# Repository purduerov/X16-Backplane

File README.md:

# Readme for X16-Backplane
This board routes signals and power between all the boards

Whenever you make a new part, download the datasheet and save it here _**and**_ with the part in the parts library

Always pull other people's changes before beginning to work
`git pull`

Be sure to push your changes after  working on them. Run:
1. `git add .` to add any files in this directory or a subdirectory
or `git add -u` to add any modified files
2. (Optional) `git clean -nX` to see what ignored files can be removed
	`git clean -fX` removes ignored files (Eagle backups)
3. `git commit -m "helpful commit message"` with a description of the work that you did
4. `git push` to push your work to github

Other helpful commands
* `git status` says information about modified and staged files
* `git log` shows the recent commits of the repository
* `git log filename.extension` show the recent commits for just that file
* `git checkout first-couple-letter-of-commit-id` lets you go back to a previous version
* `git checkout master` brings you back to the latest commit
* `git tag` lists the tags
* `git tag -a orderX -m "the version of the board placed for the X'th order"` tag a specific commit
* `git push --tags` needed to push tags to remote
* `git show orderX` show the commit log for the given tag
* `git checkout orderX` go back and interact with the files at the tagged commit

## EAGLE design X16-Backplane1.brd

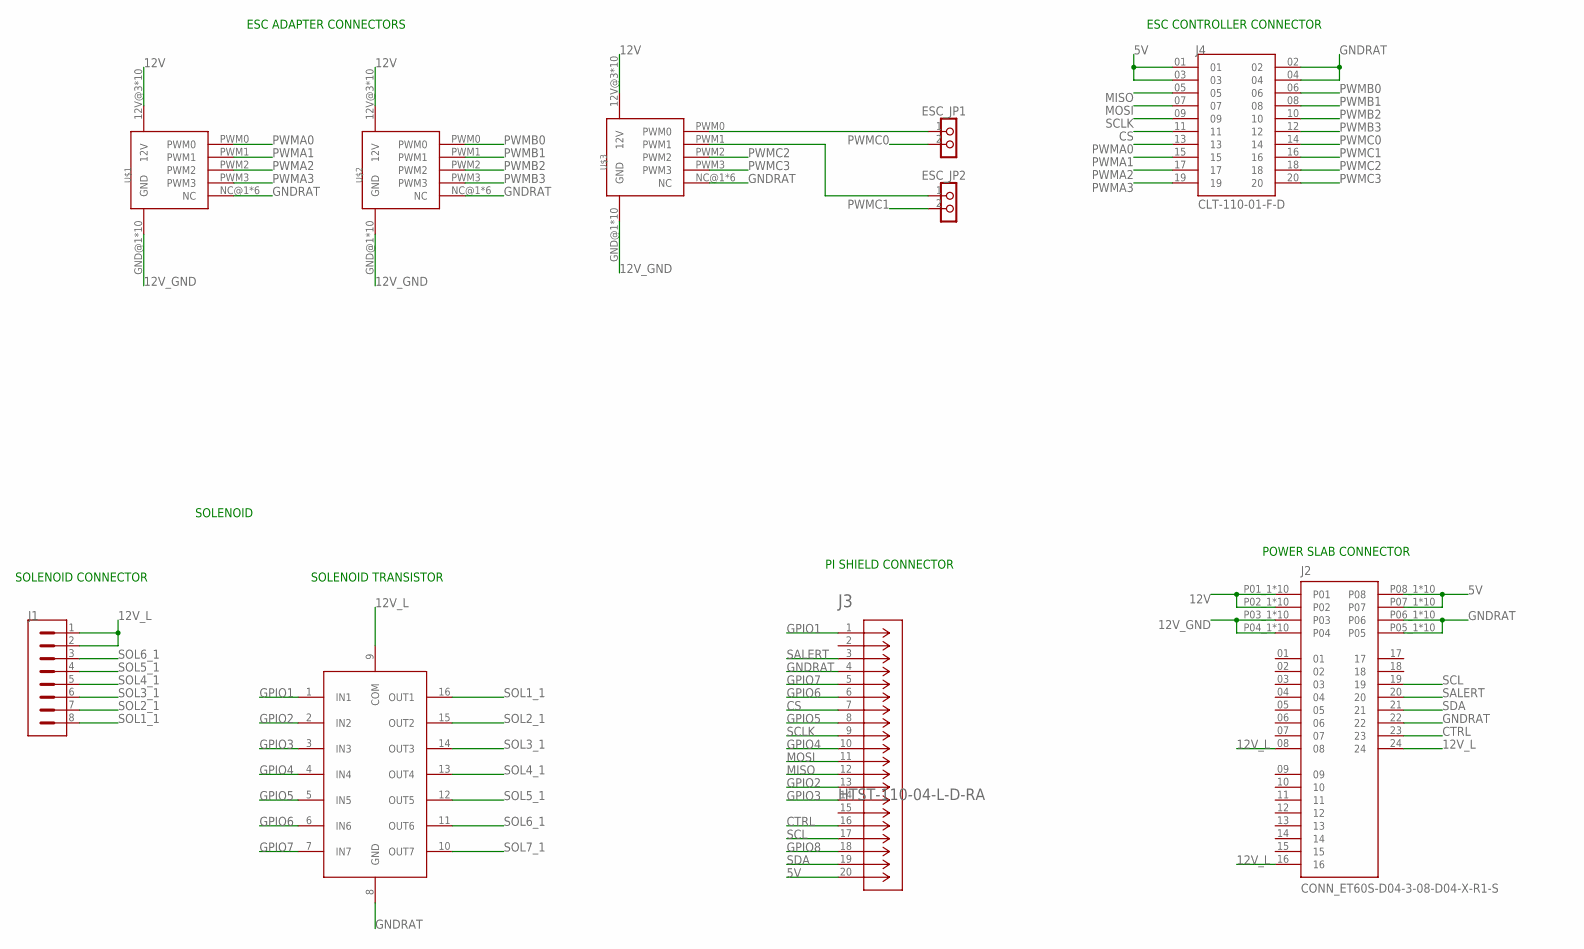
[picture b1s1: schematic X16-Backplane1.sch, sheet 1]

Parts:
ESC_JP1, ESC_JP2: TEST_PIN-1X2; 1X02
J1: CONN_PXC-8-RA-1778683; PXC-8-RA-1778683
J2: CONN_ET60S-D04-3-08-D04-X-R1-S; SAMTEC_ET60S-D04-3-08-D04-X-R1-S
J3: HTST-110-04-L-D-RA; CONN_HTST-110-04/05-X-D-RA_SAI
J4: CLT-110-01-F-D; SAMTEC_CLT-110-01-F-D
U2: TRANS_ULN2003AD; 16-SOIC
U$1, U$2, U$3: CONN_BACKPLANE_ESC_ADAPTER_NEW; CONN_BACKPLANE_ESC_ADAPTER

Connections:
5V: J2.P07_1 (P07), J2.P07_2 (P07), J2.P07_3 (P07), J2.P07_4 (P07), J2.P07_5 (P07), J2.P07_6 (P07), J2.P07_7 (P07), J2.P07_8 (P07), J2.P07_9 (P07), J2.P07_10 (P07), J2.P08_1 (P08), J2.P08_2 (P08), J2.P08_3 (P08), J2.P08_4 (P08), J2.P08_5 (P08), J2.P08_6 (P08), J2.P08_7 (P08), J2.P08_8 (P08), J2.P08_9 (P08), J2.P08_10 (P08), J3.20, J4.01, J4.03; also elsewhere on the board
12V: J2.P01_1 (P01), J2.P01_2 (P01), J2.P01_3 (P01), J2.P01_4 (P01), J2.P01_5 (P01), J2.P01_6 (P01), J2.P01_7 (P01), J2.P01_8 (P01), J2.P01_9 (P01), J2.P01_10 (P01), J2.P02_1 (P02), J2.P02_2 (P02), J2.P02_3 (P02), J2.P02_4 (P02), J2.P02_5 (P02), J2.P02_6 (P02), J2.P02_7 (P02), J2.P02_8 (P02), J2.P02_9 (P02), J2.P02_10 (P02), U$1.12V@3 (12V), U$1.12V@4 (12V), U$1.12V@5 (12V), U$1.12V@6 (12V), U$1.12V@7 (12V), U$1.12V@8 (12V), U$1.12V@9 (12V), U$1.12V@10 (12V), U$1.12V@11 (12V), U$1.12V@12 (12V), U$2.12V@3 (12V), U$2.12V@4 (12V), U$2.12V@5 (12V), U$2.12V@6 (12V), U$2.12V@7 (12V), U$2.12V@8 (12V), U$2.12V@9 (12V), U$2.12V@10 (12V), U$2.12V@11 (12V), U$2.12V@12 (12V), U$3.12V@3 (12V), U$3.12V@4 (12V), U$3.12V@5 (12V), U$3.12V@6 (12V), U$3.12V@7 (12V), U$3.12V@8 (12V), U$3.12V@9 (12V), U$3.12V@10 (12V), U$3.12V@11 (12V), U$3.12V@12 (12V); also elsewhere on the board
12V_GND: J2.P03_1 (P03), J2.P03_2 (P03), J2.P03_3 (P03), J2.P03_4 (P03), J2.P03_5 (P03), J2.P03_6 (P03), J2.P03_7 (P03), J2.P03_8 (P03), J2.P03_9 (P03), J2.P03_10 (P03), J2.P04_1 (P04), J2.P04_2 (P04), J2.P04_3 (P04), J2.P04_4 (P04), J2.P04_5 (P04), J2.P04_6 (P04), J2.P04_7 (P04), J2.P04_8 (P04), J2.P04_9 (P04), J2.P04_10 (P04), U$1.GND@1 (GND), U$1.GND@2 (GND), U$1.GND@3 (GND), U$1.GND@4 (GND), U$1.GND@5 (GND), U$1.GND@6 (GND), U$1.GND@7 (GND), U$1.GND@8 (GND), U$1.GND@9 (GND), U$1.GND@10 (GND), U$2.GND@1 (GND), U$2.GND@2 (GND), U$2.GND@3 (GND), U$2.GND@4 (GND), U$2.GND@5 (GND), U$2.GND@6 (GND), U$2.GND@7 (GND), U$2.GND@8 (GND), U$2.GND@9 (GND), U$2.GND@10 (GND), U$3.GND@1 (GND), U$3.GND@2 (GND), U$3.GND@3 (GND), U$3.GND@4 (GND), U$3.GND@5 (GND), U$3.GND@6 (GND), U$3.GND@7 (GND), U$3.GND@8 (GND), U$3.GND@9 (GND), U$3.GND@10 (GND); also elsewhere on the board
12V_L: J1.1, J1.2, J2.08, J2.16, J2.24, U2.9 (COM)
CS: J3.7, J4.11; also elsewhere on the board
CTRL: J2.23, J3.16
GNDRAT: J2.22, J2.P05_1 (P05), J2.P05_2 (P05), J2.P05_3 (P05), J2.P05_4 (P05), J2.P05_5 (P05), J2.P05_6 (P05), J2.P05_7 (P05), J2.P05_8 (P05), J2.P05_9 (P05), J2.P05_10 (P05), J2.P06_1 (P06), J2.P06_2 (P06), J2.P06_3 (P06), J2.P06_4 (P06), J2.P06_5 (P06), J2.P06_6 (P06), J2.P06_7 (P06), J2.P06_8 (P06), J2.P06_9 (P06), J2.P06_10 (P06), J3.4, J4.02, J4.04, U2.8 (GND), U$1.NC@1 (NC), U$1.NC@2 (NC), U$1.NC@3 (NC), U$1.NC@4 (NC), U$1.NC@5 (NC), U$1.NC@6 (NC), U$2.NC@1 (NC), U$2.NC@2 (NC), U$2.NC@3 (NC), U$2.NC@4 (NC), U$2.NC@5 (NC), U$2.NC@6 (NC), U$3.NC@1 (NC), U$3.NC@2 (NC), U$3.NC@3 (NC), U$3.NC@4 (NC), U$3.NC@5 (NC), U$3.NC@6 (NC); also elsewhere on the board
GPIO1: J3.1, U2.1 (IN1)
GPIO2: J3.13, U2.2 (IN2)
GPIO3: J3.14, U2.3 (IN3)
GPIO4: J3.10, U2.4 (IN4)
GPIO5: J3.8, U2.5 (IN5)
GPIO6: J3.6, U2.6 (IN6)
GPIO7: J3.5, U2.7 (IN7)
GPIO8: J3.18
MISO: J3.12, J4.05; also elsewhere on the board
MOSI: J3.11, J4.07; also elsewhere on the board
unnamed: ESC_JP1.1, U$3.PWM0
unnamed: ESC_JP2.1, U$3.PWM1
PWMA0: J4.13, U$1.PWM0
PWMA1: J4.15, U$1.PWM1
PWMA2: J4.17, U$1.PWM2
PWMA3: J4.19, U$1.PWM3
PWMB0: J4.06, U$2.PWM0
PWMB1: J4.08, U$2.PWM1
PWMB2: J4.10, U$2.PWM2
PWMB3: J4.12, U$2.PWM3
PWMC0: ESC_JP1.2, J4.14; also elsewhere on the board
PWMC1: ESC_JP2.2, J4.16; also elsewhere on the board
PWMC2: J4.18, U$3.PWM2
PWMC3: J4.20, U$3.PWM3
SALERT: J2.20, J3.3
SCL: J2.19, J3.17
SCLK: J3.9, J4.09; also elsewhere on the board
SDA: J2.21, J3.19
SOL1_1: J1.8, U2.16 (OUT1)
SOL2_1: J1.7, U2.15 (OUT2)
SOL3_1: J1.6, U2.14 (OUT3)
SOL4_1: J1.5, U2.13 (OUT4)
SOL5_1: J1.4, U2.12 (OUT5)
SOL6_1: J1.3, U2.11 (OUT6)
SOL7_1: U2.10 (OUT7)

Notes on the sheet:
ESC ADAPTER CONNECTORS
SOLENOID
POWER SLAB CONNECTOR
SOLENOID TRANSISTOR
SOLENOID CONNECTOR
ESC CONTROLLER CONNECTOR
PI SHIELD CONNECTOR

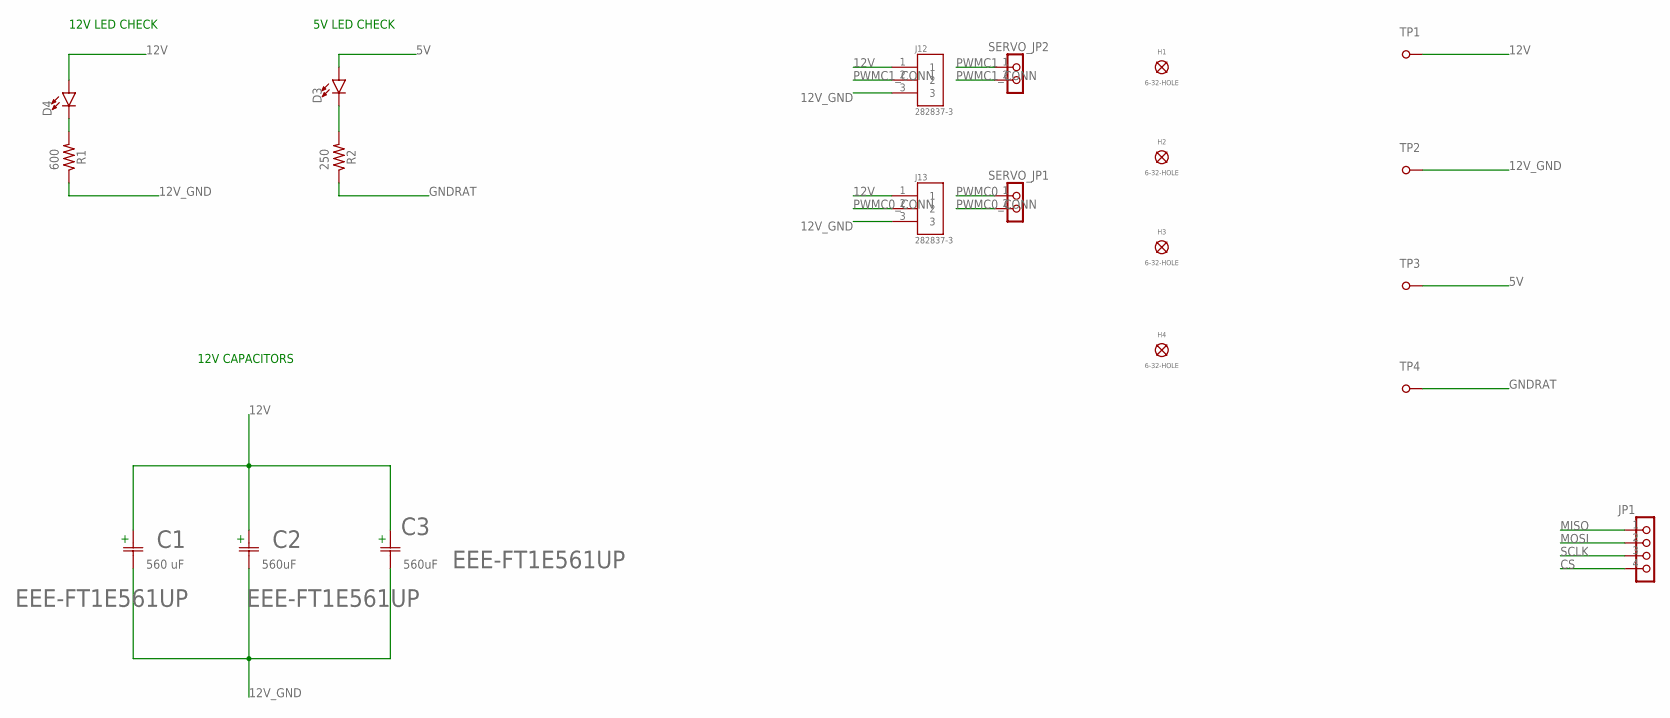
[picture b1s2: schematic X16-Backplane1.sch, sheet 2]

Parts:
C1, C2, C3: EEE-FT1E561UP; CAP_FT_F_PAN
D3, D4: LEDCHIPLED_0805; CHIPLED_0805
H1, H2, H3, H4: 6-32-HOLE
J12, J13: 282837-3; TE_282837-3
JP1: TEST_PIN-1X4; 1X04
R1, R2: 0603
SERVO_JP1, SERVO_JP2: TEST_PIN-1X2; 1X02
TP1, TP2, TP3, TP4: TESTPOINT_5.04MM

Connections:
5V: D3.A, TP3.TP; also elsewhere on the board
12V: C1.1, C2.1, C3.1, D4.A, J12.1, J13.1, TP1.TP; also elsewhere on the board
12V_GND: C1.2, C2.2, C3.2, J12.3, J13.3, R1.1, TP2.TP; also elsewhere on the board
CS: JP1.4; also elsewhere on the board
GNDRAT: R2.1, TP4.TP; also elsewhere on the board
MISO: JP1.1; also elsewhere on the board
MOSI: JP1.2; also elsewhere on the board
unnamed: D4.C, R1.2
unnamed: D3.C, R2.2
PWMC0: SERVO_JP1.1; also elsewhere on the board
PWMC0_CONN: J13.2, SERVO_JP1.2
PWMC1: SERVO_JP2.1; also elsewhere on the board
PWMC1_CONN: J12.2, SERVO_JP2.2
SCLK: JP1.3; also elsewhere on the board

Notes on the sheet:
12V LED CHECK
5V LED CHECK
12V CAPACITORS

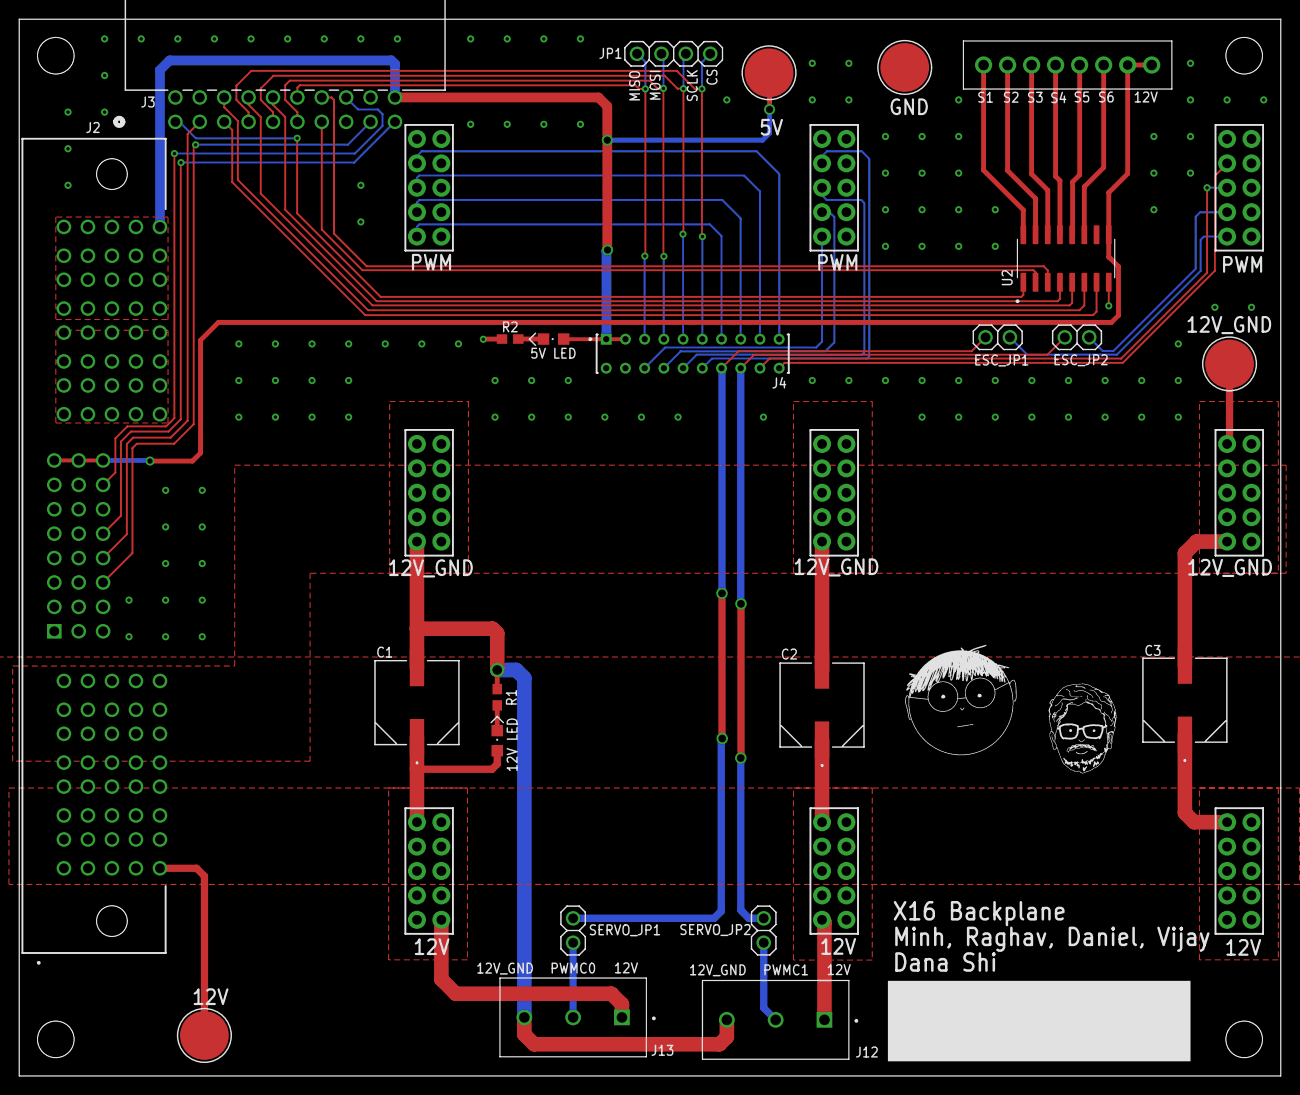
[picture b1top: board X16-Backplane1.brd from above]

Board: 2 copper layers, 131.3 x 110.0 mm, 30 parts (0 on the bottom side), 44 nets.

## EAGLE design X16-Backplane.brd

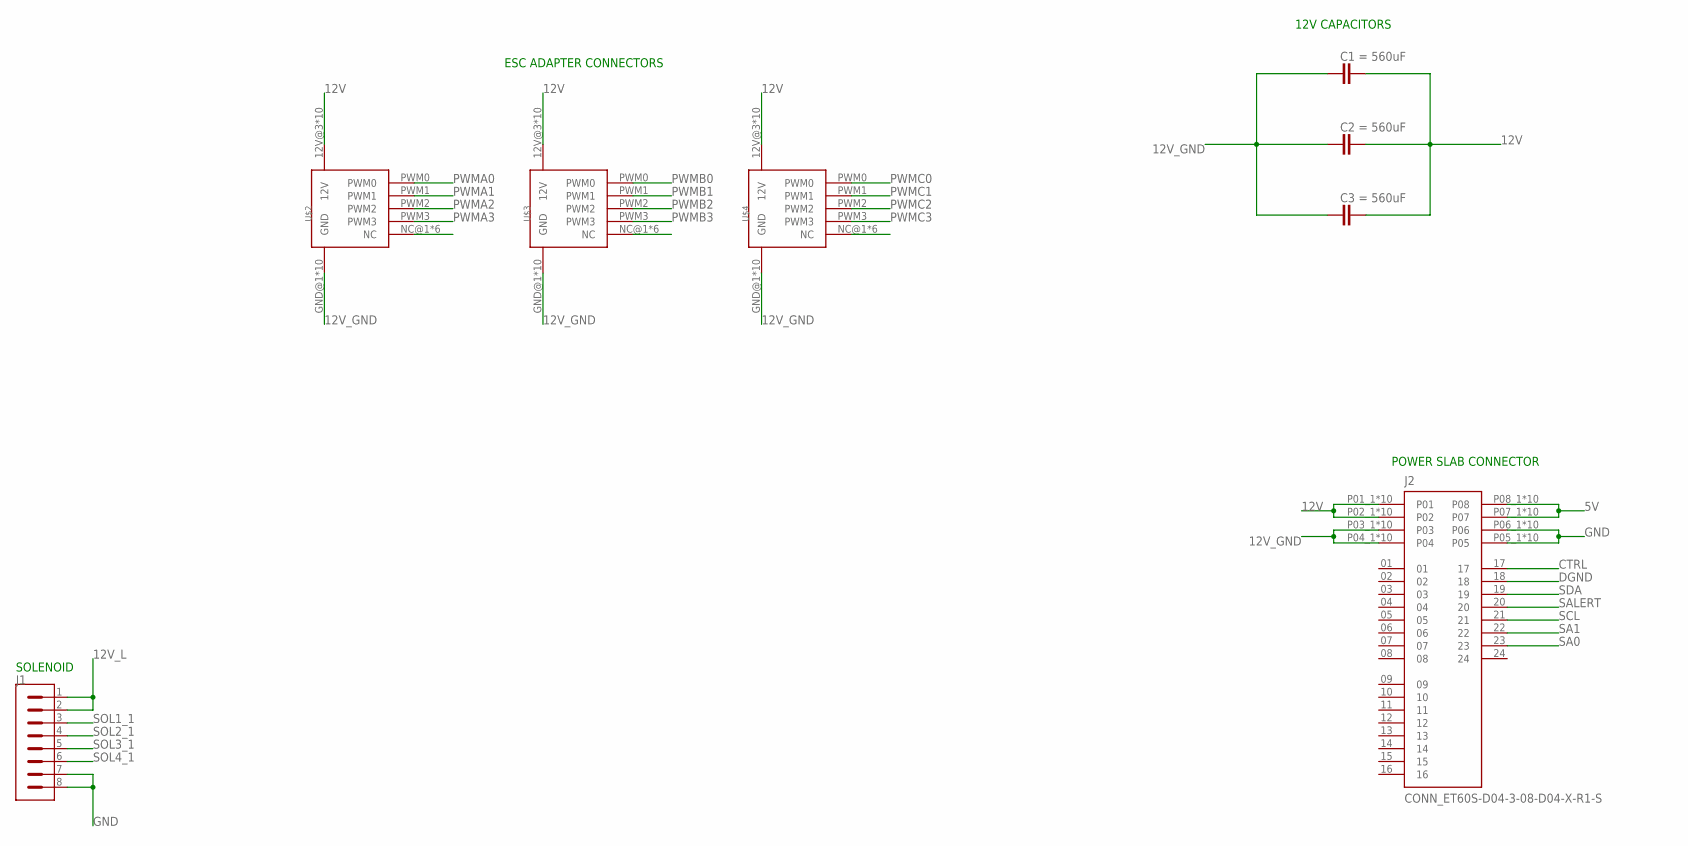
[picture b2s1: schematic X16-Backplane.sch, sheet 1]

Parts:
J1: CONN_PXC-8-RA-1778683; PXC-8-RA-1778683
J2: CONN_ET60S-D04-3-08-D04-X-R1-S; SAMTEC_ET60S-D04-3-08-D04-X-R1-S
U$2, U$3, U$4: CONN_BACKPLANE_ESC_ADAPTER

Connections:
5V: J2.P07_1 (P07), J2.P07_2 (P07), J2.P07_3 (P07), J2.P07_4 (P07), J2.P07_5 (P07), J2.P07_6 (P07), J2.P07_7 (P07), J2.P07_8 (P07), J2.P07_9 (P07), J2.P07_10 (P07), J2.P08_1 (P08), J2.P08_2 (P08), J2.P08_3 (P08), J2.P08_4 (P08), J2.P08_5 (P08), J2.P08_6 (P08), J2.P08_7 (P08), J2.P08_8 (P08), J2.P08_9 (P08), J2.P08_10 (P08); also elsewhere on the board
12V: J2.P01_1 (P01), J2.P01_2 (P01), J2.P01_3 (P01), J2.P01_4 (P01), J2.P01_5 (P01), J2.P01_6 (P01), J2.P01_7 (P01), J2.P01_8 (P01), J2.P01_9 (P01), J2.P01_10 (P01), J2.P02_1 (P02), J2.P02_2 (P02), J2.P02_3 (P02), J2.P02_4 (P02), J2.P02_5 (P02), J2.P02_6 (P02), J2.P02_7 (P02), J2.P02_8 (P02), J2.P02_9 (P02), J2.P02_10 (P02), U$2.12V@3 (12V), U$2.12V@4 (12V), U$2.12V@5 (12V), U$2.12V@6 (12V), U$2.12V@7 (12V), U$2.12V@8 (12V), U$2.12V@9 (12V), U$2.12V@10 (12V), U$2.12V@11 (12V), U$2.12V@12 (12V), U$3.12V@3 (12V), U$3.12V@4 (12V), U$3.12V@5 (12V), U$3.12V@6 (12V), U$3.12V@7 (12V), U$3.12V@8 (12V), U$3.12V@9 (12V), U$3.12V@10 (12V), U$3.12V@11 (12V), U$3.12V@12 (12V), U$4.12V@3 (12V), U$4.12V@4 (12V), U$4.12V@5 (12V), U$4.12V@6 (12V), U$4.12V@7 (12V), U$4.12V@8 (12V), U$4.12V@9 (12V), U$4.12V@10 (12V), U$4.12V@11 (12V), U$4.12V@12 (12V); also elsewhere on the board
12V_GND: J2.P03_1 (P03), J2.P03_2 (P03), J2.P03_3 (P03), J2.P03_4 (P03), J2.P03_5 (P03), J2.P03_6 (P03), J2.P03_7 (P03), J2.P03_8 (P03), J2.P03_9 (P03), J2.P03_10 (P03), J2.P04_1 (P04), J2.P04_2 (P04), J2.P04_3 (P04), J2.P04_4 (P04), J2.P04_5 (P04), J2.P04_6 (P04), J2.P04_7 (P04), J2.P04_8 (P04), J2.P04_9 (P04), J2.P04_10 (P04), U$2.GND@1 (GND), U$2.GND@2 (GND), U$2.GND@3 (GND), U$2.GND@4 (GND), U$2.GND@5 (GND), U$2.GND@6 (GND), U$2.GND@7 (GND), U$2.GND@8 (GND), U$2.GND@9 (GND), U$2.GND@10 (GND), U$3.GND@1 (GND), U$3.GND@2 (GND), U$3.GND@3 (GND), U$3.GND@4 (GND), U$3.GND@5 (GND), U$3.GND@6 (GND), U$3.GND@7 (GND), U$3.GND@8 (GND), U$3.GND@9 (GND), U$3.GND@10 (GND), U$4.GND@1 (GND), U$4.GND@2 (GND), U$4.GND@3 (GND), U$4.GND@4 (GND), U$4.GND@5 (GND), U$4.GND@6 (GND), U$4.GND@7 (GND), U$4.GND@8 (GND), U$4.GND@9 (GND), U$4.GND@10 (GND)
12V_L: J1.1, J1.2; also elsewhere on the board
CTRL: J2.17; also elsewhere on the board
DGND: J2.18; also elsewhere on the board
GND: J1.7, J1.8, J2.P05_1 (P05), J2.P05_2 (P05), J2.P05_3 (P05), J2.P05_4 (P05), J2.P05_5 (P05), J2.P05_6 (P05), J2.P05_7 (P05), J2.P05_8 (P05), J2.P05_9 (P05), J2.P05_10 (P05), J2.P06_1 (P06), J2.P06_2 (P06), J2.P06_3 (P06), J2.P06_4 (P06), J2.P06_5 (P06), J2.P06_6 (P06), J2.P06_7 (P06), J2.P06_8 (P06), J2.P06_9 (P06), J2.P06_10 (P06); also elsewhere on the board
unnamed: U$2.NC@1 (NC), U$2.NC@2 (NC), U$2.NC@3 (NC), U$2.NC@4 (NC), U$2.NC@5 (NC), U$2.NC@6 (NC)
unnamed: U$3.NC@1 (NC), U$3.NC@2 (NC), U$3.NC@3 (NC), U$3.NC@4 (NC), U$3.NC@5 (NC), U$3.NC@6 (NC)
unnamed: U$4.NC@1 (NC), U$4.NC@2 (NC), U$4.NC@3 (NC), U$4.NC@4 (NC), U$4.NC@5 (NC), U$4.NC@6 (NC)
PWMA0: U$2.PWM0
PWMA1: U$2.PWM1
PWMA2: U$2.PWM2
PWMA3: U$2.PWM3
PWMB0: U$3.PWM0
PWMB1: U$3.PWM1
PWMB2: U$3.PWM2
PWMB3: U$3.PWM3
PWMC0: U$4.PWM0
PWMC1: U$4.PWM1
PWMC2: U$4.PWM2
PWMC3: U$4.PWM3
SA0: J2.23; also elsewhere on the board
SA1: J2.22; also elsewhere on the board
SALERT: J2.20; also elsewhere on the board
SCL: J2.21; also elsewhere on the board
SDA: J2.19; also elsewhere on the board
SOL1_1: J1.3; also elsewhere on the board
SOL2_1: J1.4; also elsewhere on the board
SOL3_1: J1.5; also elsewhere on the board
SOL4_1: J1.6; also elsewhere on the board

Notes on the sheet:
SOLENOID
POWER SLAB CONNECTOR
ESC ADAPTER CONNECTORS
12V CAPACITORS

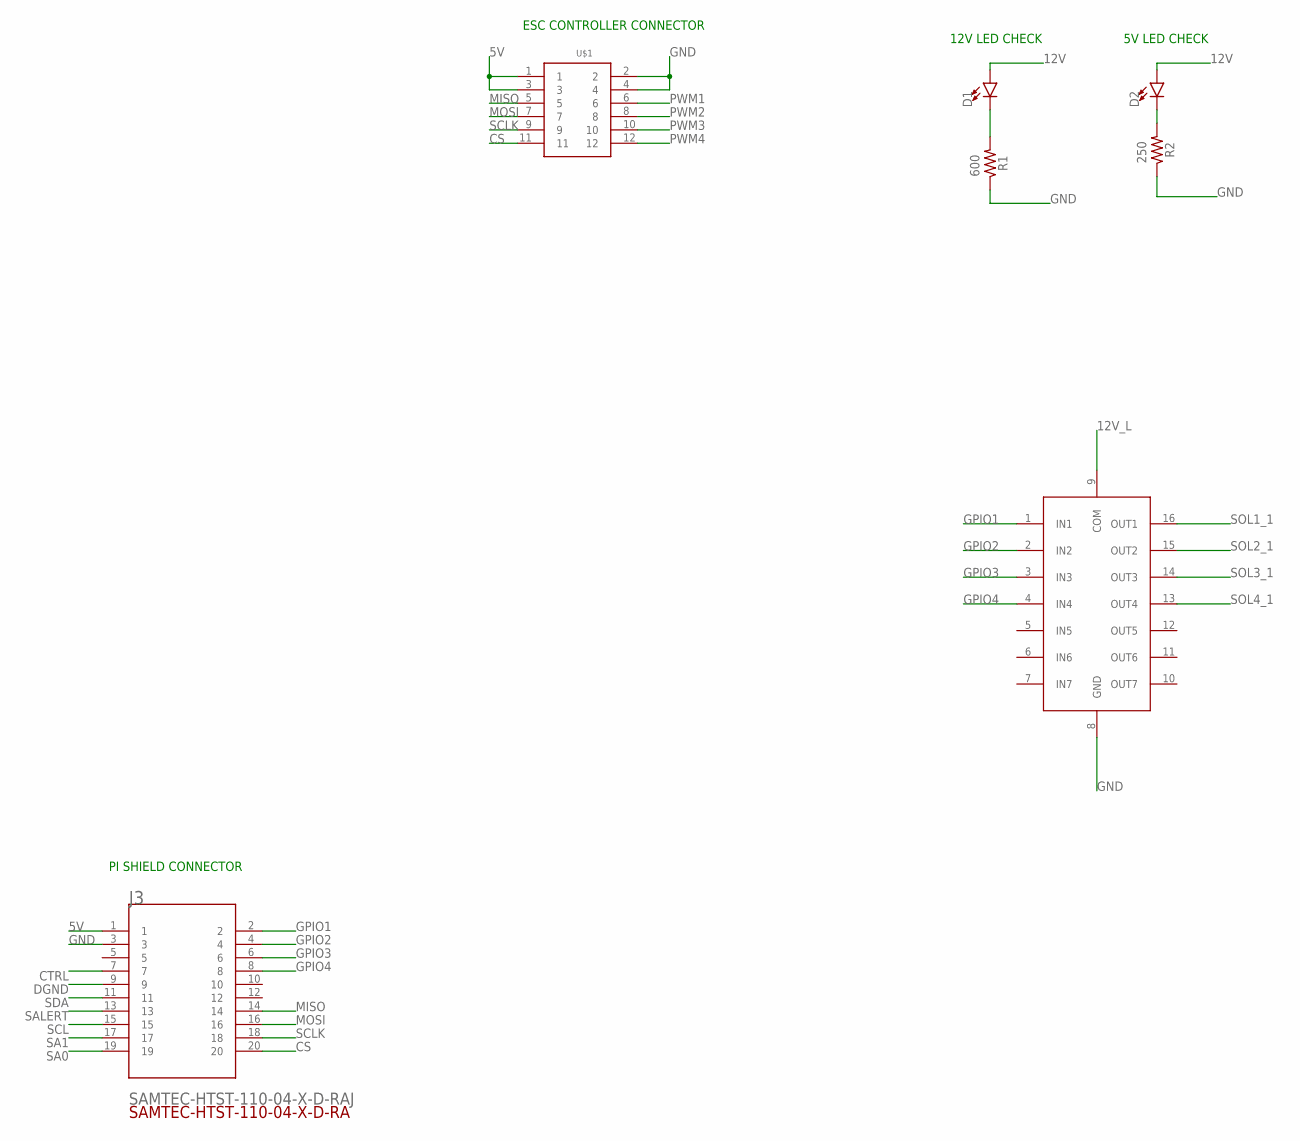
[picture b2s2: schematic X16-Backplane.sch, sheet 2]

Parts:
D1, D2: LED0603; LED-0603
J3: SAMTEC-HTST-110-04-X-D-RAJ; SAMTEC-HTST-110-04-X-D-RA
R1, R2: 0603
U1: TRANS_ULN2003AD; 16-SOIC
U$1: CONN_BACKPLANE_ESC_CONTROLLERBKP; BACKPLANE_CONNECTORS_BKP

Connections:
5V: J3.1, U$1.1, U$1.3; also elsewhere on the board
12V: D1.A, D2.A; also elsewhere on the board
12V_L: U1.9 (COM); also elsewhere on the board
CS: J3.20, U$1.11
CTRL: J3.7; also elsewhere on the board
DGND: J3.9; also elsewhere on the board
GND: J3.3, R1.1, R2.1, U1.8 (GND), U$1.2, U$1.4; also elsewhere on the board
GPIO1: J3.2, U1.1 (IN1)
GPIO2: J3.4, U1.2 (IN2)
GPIO3: J3.6, U1.3 (IN3)
GPIO4: J3.8, U1.4 (IN4)
MISO: J3.14, U$1.5
MOSI: J3.16, U$1.7
unnamed: D1.C, R1.2
unnamed: D2.C, R2.2
PWM1: U$1.6
PWM2: U$1.8
PWM3: U$1.10
PWM4: U$1.12
SA0: J3.19; also elsewhere on the board
SA1: J3.17; also elsewhere on the board
SALERT: J3.13; also elsewhere on the board
SCL: J3.15; also elsewhere on the board
SCLK: J3.18, U$1.9
SDA: J3.11; also elsewhere on the board
SOL1_1: U1.16 (OUT1); also elsewhere on the board
SOL2_1: U1.15 (OUT2); also elsewhere on the board
SOL3_1: U1.14 (OUT3); also elsewhere on the board
SOL4_1: U1.13 (OUT4); also elsewhere on the board

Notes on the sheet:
ESC CONTROLLER CONNECTOR
PI SHIELD CONNECTOR
12V LED CHECK
5V LED CHECK

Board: 2 copper layers, 12 parts (0 on the bottom side), 29 nets, no tracks yet.

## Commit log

2023-08-30 added tentative dimensions
2023-09-23 Added .gitignore file
2023-09-28 9/27/2023
2023-09-30 09/30/2023
2023-09-30 9/30/2023
2023-10-11 Added board dimensions and removed unneeded files
2023-10-11 schematic_complete?
2023-10-14 10/14 sch issues fixed
2023-11-04 Added new backplane to pi connector to use that has enough pins in footprint
2023-12-20 Minh Update 2
2023-12-20 Minh Update 1
2023-12-21 Minh Update 3
2023-12-21 few extra labels and got rid of wire stubs from drc
2023-12-23 Minh Update 4
2023-12-23 Revert "Minh Update 4"
    This reverts commit 6540dcb78246fca95661c726553611ac5071b16d.
2023-12-23 Minh Update 5
2023-12-29 Minh Update 6
2023-12-29 Minh Update 7
2023-12-30 GERBER file created

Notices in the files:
parts and their libraries:
SparkFun-LED: Licensing: Creative Commons ShareAlike 4.0 International - https://creativecommons.org/licenses/by-sa/4.0
COPYRIGHT: Copyright (C) 2023 Ultra Librarian. All rights reserved.
